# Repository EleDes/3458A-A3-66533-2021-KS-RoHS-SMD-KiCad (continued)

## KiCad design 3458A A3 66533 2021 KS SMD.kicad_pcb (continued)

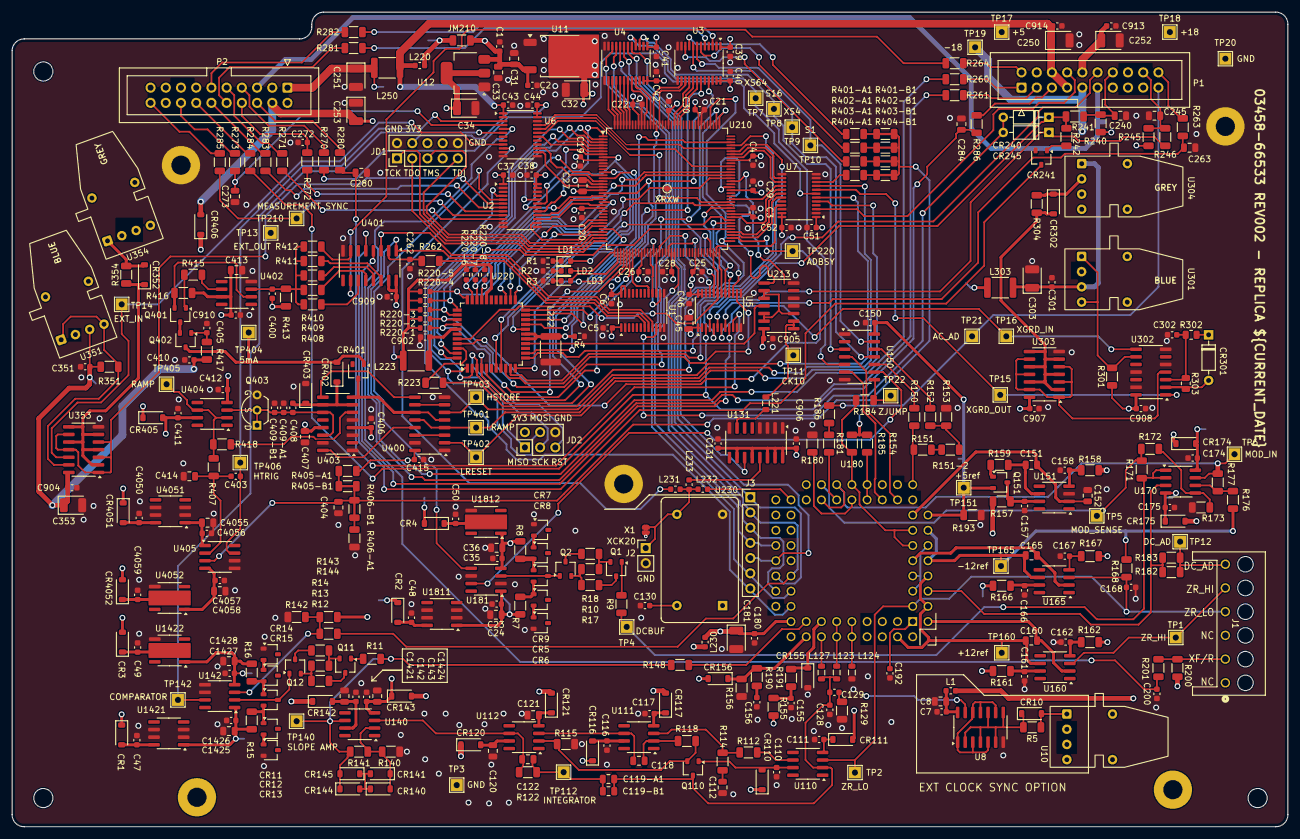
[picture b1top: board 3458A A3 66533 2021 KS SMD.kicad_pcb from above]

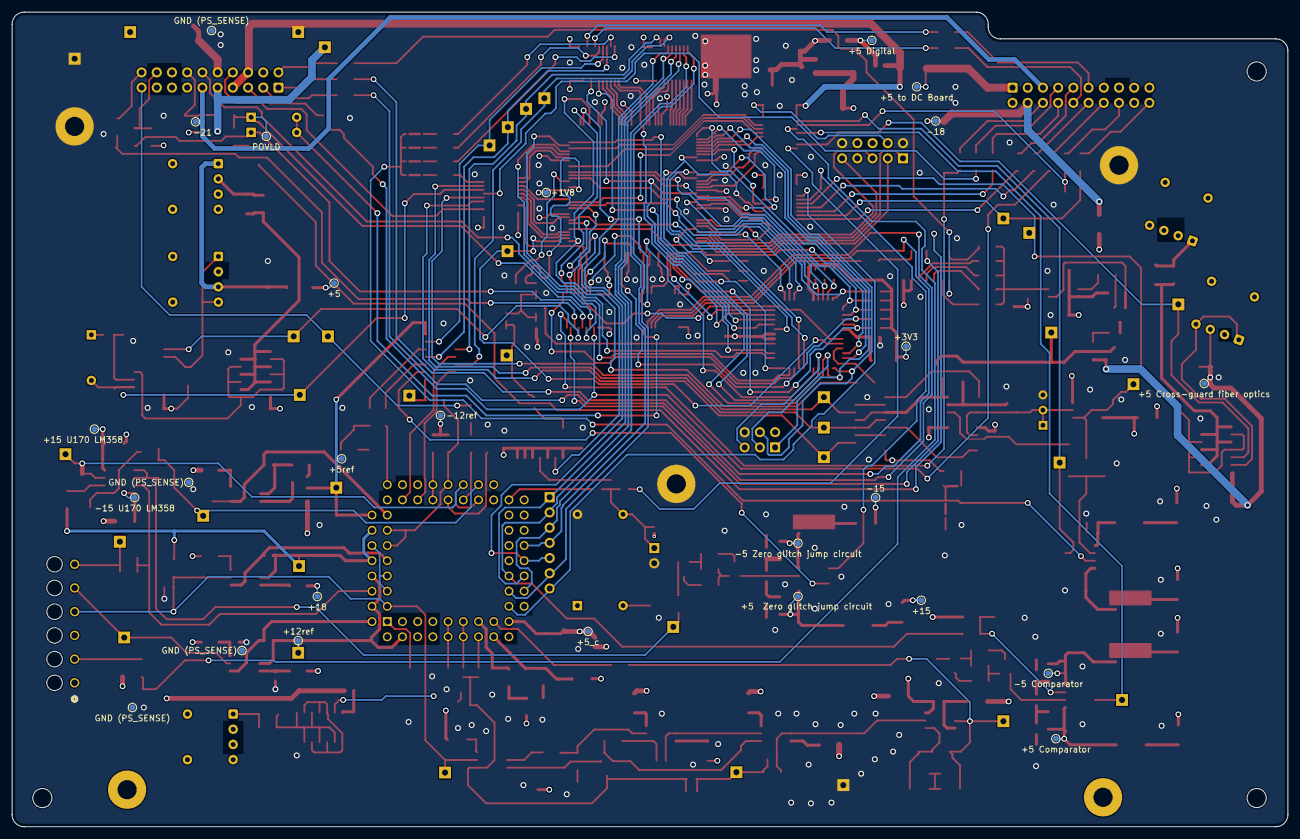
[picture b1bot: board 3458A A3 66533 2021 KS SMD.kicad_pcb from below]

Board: 4 copper layers, 213.0 x 136.0 mm, 448 parts (26 on the bottom side), 328 nets.

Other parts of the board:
+1V8, +3V3, +5, +5  Zero glitch jump circuit, +5 Comparator, +5 Cross-guard fiber optics, +5 Digital, +5 to DC Board, +5_c, +5ref, +12ref, +15, +15 U170 LM358, +18: TestPoint_Small; TestPoint_Pad_D1.0mm
-5 Comparator, -5 Zero glitch jump circuit, -12ref, -15, -15 U170 LM358, -18, -21: TestPoint_Small; TestPoint_Pad_D1.0mm
GND (PS_SENSE): TestPoint_Small; TestPoint_Pad_D1.0mm
GND (PS_SENSE)#2, GND (PS_SENSE)#3, GND (PS_SENSE)#4: TestPoint_Small; TestPoint_Pad_D1.0mm
POVLD: TestPoint_Small; TestPoint_Pad_D1.0mm
XRXW: TestPoint_Small; TestPoint_Pad_D1.0mm

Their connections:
+1V8: +1V8.1; also elsewhere on the board
+3V3: +3V3.1; also elsewhere on the board
+5: +5.1; also elsewhere on the board
+5_F: +5 to DC Board.1; also elsewhere on the board
+5_R: +5 Comparator.1; also elsewhere on the board
+5_Z: +5 Zero glitch jump circuit.1; also elsewhere on the board
+5_a: +5 Digital.1; also elsewhere on the board
+5_b: +5 Cross-guard fiber optics.1; also elsewhere on the board
+5_c: +5_c.1; also elsewhere on the board
+5ref: +5ref.1; also elsewhere on the board
+12ref: +12ref.1; also elsewhere on the board
+15: +15.1; also elsewhere on the board
+18: +18.1; also elsewhere on the board
-5_C: -5 Comparator.1; also elsewhere on the board
-5_Z: -5 Zero glitch jump circuit.1; also elsewhere on the board
-12ref: -12ref.1; also elsewhere on the board
-15: -15.1; also elsewhere on the board
-18: -18.1; also elsewhere on the board
-21: -21.1; also elsewhere on the board
/A3 IN-GRD CTL & INTERPOLATOR/CPLD & LEVEL SHIFT (Seite 2)/_XRXW: XRXW.1; also elsewhere on the board
unnamed 129: +15 U170 LM358.1; also elsewhere on the board
unnamed 130: -15 U170 LM358.1; also elsewhere on the board
POVLD: POVLD.1; also elsewhere on the board
PS_SENSE: GND (PS_SENSE).1, GND (PS_SENSE)#2.1, GND (PS_SENSE)#3.1, GND (PS_SENSE)#4.1; also elsewhere on the board

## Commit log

2025-10-19 Initial
2025-10-19 add README
2025-10-28 Corrected revision history table Following issues are addressed: Fixes #1 Fixes #2 Fixes #3 Fixes #4 Fixes #5 Fixes #6 Fixes #7 Fixes #9 Fixes #10
2025-11-19 Corrected revision history table Position of mounting holes & J1 optimized Following issues are addressed: Fixes #11
2026-04-11 Critical error fixed Fixes #14 Fixes #15 Close #8
2026-04-17 ibom updated
